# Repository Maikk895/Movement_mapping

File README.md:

Schemat projektu:

Layout płytki:

Wizualizacja:

Gotowy projekt:

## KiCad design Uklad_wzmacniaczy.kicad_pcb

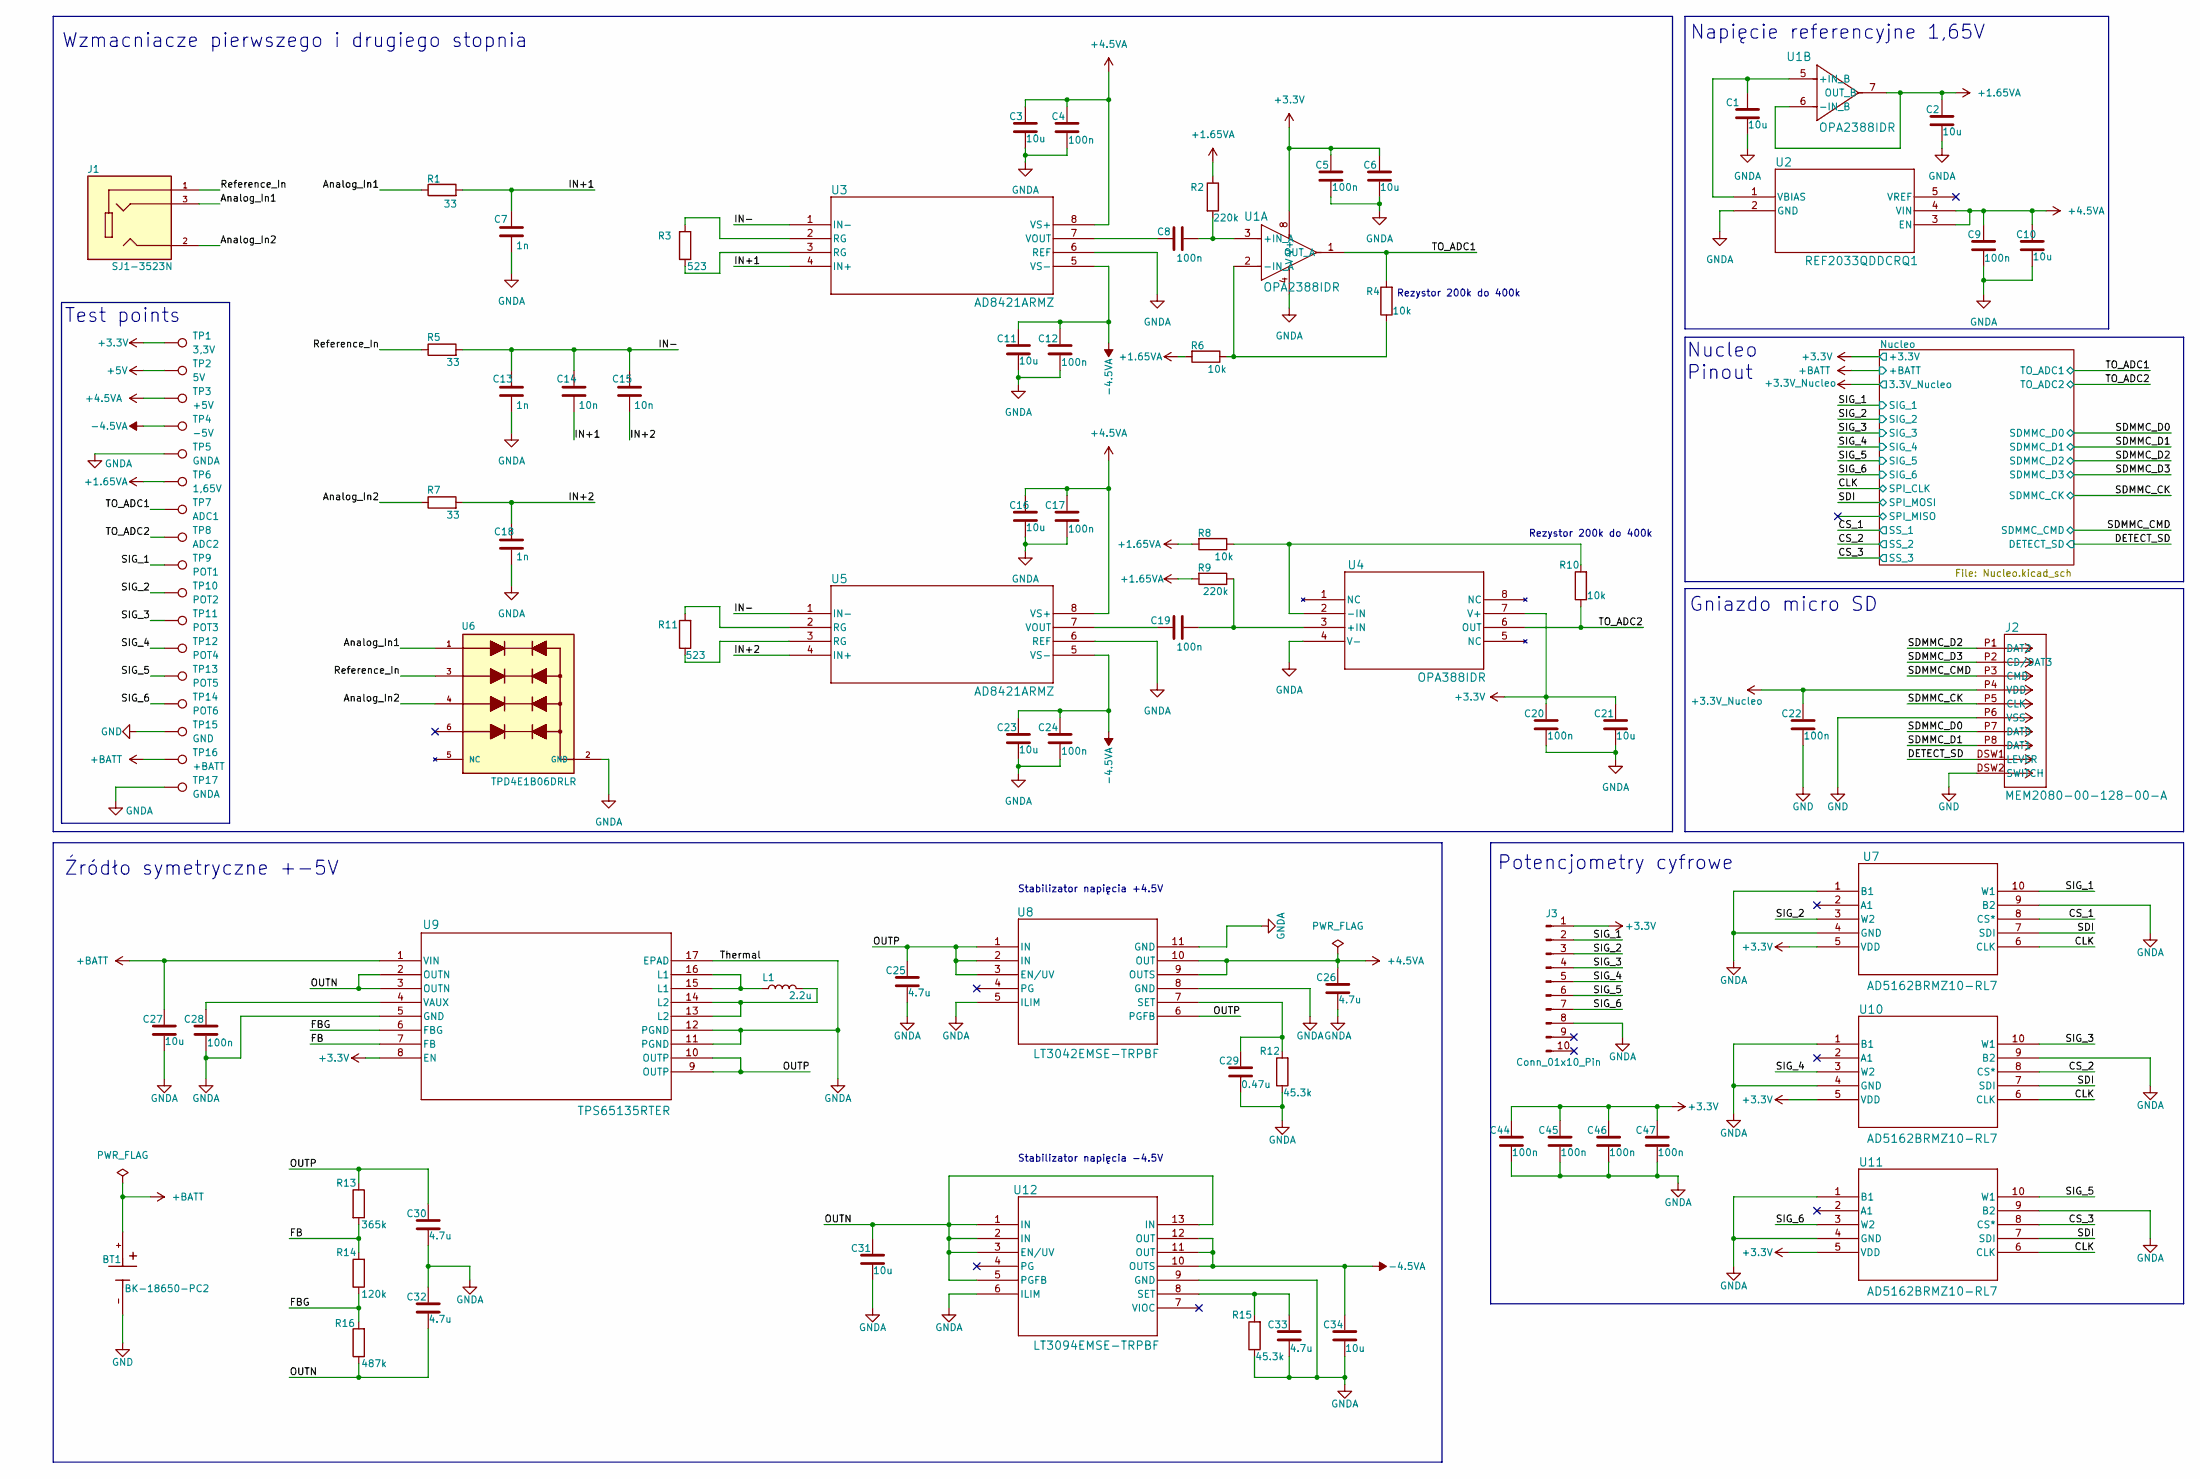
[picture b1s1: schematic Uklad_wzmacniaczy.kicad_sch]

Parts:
BT1: BK-18650-PC2; BAT_BK-18650-PC2; PARTREV F
C1, C2, C3, C6, C10, C11, C16, C21, C23, C27, C31, C34: 10u; C_0603_1608Metric_Pad1.08x0.95mm_HandSolder
C4, C5, C8, C9, C12, C17, C19, C20, C22, C24, C28, C44, C45, C46, C47: 100n; C_0603_1608Metric_Pad1.08x0.95mm_HandSolder
C7, C13, C18: 1n; C_0603_1608Metric_Pad1.08x0.95mm_HandSolder
C14, C15: 10n; C_0603_1608Metric_Pad1.08x0.95mm_HandSolder
C25, C26, C30, C32, C33: 4.7u; C_0603_1608Metric_Pad1.08x0.95mm_HandSolder
C29: 0.47u; C_0603_1608Metric_Pad1.08x0.95mm_HandSolder
J1: SJ1-3523N; CUI_SJ1-3523N; PARTREV 1.05
J2: MEM2080-00-128-00-A; CONN_MEM2080-00-128-00-A_GCT
J3: Conn_01x10_Pin; PinHeader_2x05_P2.54mm_Horizontal
L1: 2.2u; INDC2520X120N
R1, R5, R7: 33; R_0603_1608Metric_Pad0.98x0.95mm_HandSolder
R2, R9: 220k; R_0603_1608Metric_Pad0.98x0.95mm_HandSolder
R3, R11: 523; R_0603_1608Metric_Pad0.98x0.95mm_HandSolder
R4, R6, R8, R10: 10k; R_0603_1608Metric_Pad0.98x0.95mm_HandSolder
R12, R15: 45.3k; R_0603_1608Metric_Pad0.98x0.95mm_HandSolder
R13: 365k; R_0603_1608Metric_Pad0.98x0.95mm_HandSolder
R14: 120k; R_0603_1608Metric_Pad0.98x0.95mm_HandSolder
R16: 487k; R_0603_1608Metric_Pad0.98x0.95mm_HandSolder
TP1: 3,3V; TestPoint_Pad_D1.5mm
TP2: 5V; TestPoint_Pad_D1.5mm
TP3: +5V; TestPoint_Pad_D1.5mm
TP4: -5V; TestPoint_Pad_D1.5mm
TP5, TP17: GNDA; TestPoint_Pad_2.0x2.0mm
TP6: 1,65V; TestPoint_Pad_D1.5mm
TP7: ADC1; TestPoint_Pad_D1.5mm
TP8: ADC2; TestPoint_Pad_D1.5mm
TP9: POT1; TestPoint_Pad_D1.5mm
TP10: POT2; TestPoint_Pad_D1.5mm
TP11: POT3; TestPoint_Pad_D1.5mm
TP12: POT4; TestPoint_Pad_D1.5mm
TP13: POT5; TestPoint_Pad_D1.5mm
TP14: POT6; TestPoint_Pad_D1.5mm
TP15: GND; TestPoint_Pad_2.0x2.0mm
TP16: +BATT; TestPoint_Pad_D1.5mm
U1: OPA2388IDR; D0008A-IPC_A
U2: REF2033QDDCRQ1; SOT-23-THIN-5_DDC_TEX
U3, U5: AD8421ARMZ; RM_8_ADI
U4: OPA388IDR; D8_TEX
U6: TPD4E1B06DRLR; SOT50P160X60-6N; PARTREV E
U7, U10, U11: AD5162BRMZ10-RL7; RM_10_ADI
U8: LT3042EMSE-TRPBF; 05-08-1664_ADI
U9: TPS65135RTER; RTE16_1P7X1P7
U12: LT3094EMSE-TRPBF; MSE_05-08-1666_ADI

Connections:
+1.65VA: C2.1, R2.1, R6.2, R8.2, R9.2, TP6.1 (1_1), U1.6 (-IN_B), U1.7 (OUT_B)
+3.3V: C5.2, C6.1, C20.2, C21.1, C44.1, C45.1, C46.1, C47.1, J3.1, TP1.1 (1_1), U1.8 (V+), U4.7 (V+), U7.5 (VDD), U9.8 (EN), U10.5 (VDD), U11.5 (VDD); also elsewhere on the board
+3.3V_Nucleo: C22.1, J2.P4 (VDD); also elsewhere on the board
+5V: TP2.1 (1_1); also elsewhere on the board
+5VA: C3.1, C4.2, C9.1, C10.1, C16.1, C17.2, C26.1, TP3.1 (1_1), U2.3 (EN), U2.4 (VIN), U3.8 (VS+), U5.8 (VS+), U8.9 (OUTS), U8.10 (OUT)
+BATT: BT1.+, C27.1, TP16.1 (1_1), U9.1 (VIN); also elsewhere on the board
-5VA: C11.1, C12.2, C23.1, C24.2, C34.1, TP4.1 (1_1), U3.5 (VS-), U5.5 (VS-), U12.10 (OUTS), U12.11 (OUT), U12.12 (OUT)
/Analog_In1: J1.3, R1.1, U6.1
/Analog_In2: J1.2, R7.1, U6.4
/CLK: U7.6 (CLK), U10.6 (CLK), U11.6 (CLK); also elsewhere on the board
/CS_1: U7.8 (CS*); also elsewhere on the board
/CS_2: U10.8 (CS*); also elsewhere on the board
/CS_3: U11.8 (CS*); also elsewhere on the board
/DETECT_SD: J2.DSW1 (LEVER); also elsewhere on the board
/FB: R13.2, R14.2, U9.7 (FB)
/FBG: R14.1, R16.2, U9.6 (FBG)
/IN+1: C7.1, C14.2, R1.2, U3.4 (IN+)
/IN+2: C15.2, C18.1, R7.2, U5.4 (IN+)
/IN-: C13.1, C14.1, C15.1, R5.2, U3.1 (IN-), U5.1 (IN-)
/OUTN: C31.1, C32.2, R16.1, U9.2 (OUTN), U9.3 (OUTN), U12.1 (IN), U12.2 (IN), U12.3 (EN/UV), U12.5 (PGFB), U12.13 (IN)
/OUTP: C25.1, C30.1, R13.1, U8.1 (IN), U8.2 (IN), U8.3 (EN/UV), U8.6 (PGFB), U9.9 (OUTP), U9.10 (OUTP)
/Reference_In: J1.1, R5.1, U6.3
/SDI: U7.7 (SDI), U10.7 (SDI), U11.7 (SDI); also elsewhere on the board
/SDMMC_CK: J2.P5 (CLK); also elsewhere on the board
/SDMMC_CMD: J2.P3 (CMD); also elsewhere on the board
/SDMMC_D0: J2.P7 (DAT0); also elsewhere on the board
/SDMMC_D1: J2.P8 (DAT1); also elsewhere on the board
/SDMMC_D2: J2.P1 (DAT2); also elsewhere on the board
/SDMMC_D3: J2.P2 (CD/DAT3); also elsewhere on the board
/SIG_1: J3.2, TP9.1 (1_1), U7.10 (W1); also elsewhere on the board
/SIG_2: J3.3, TP10.1 (1_1), U7.3 (W2); also elsewhere on the board
/SIG_3: J3.4, TP11.1 (1_1), U10.10 (W1); also elsewhere on the board
/SIG_4: J3.5, TP12.1 (1_1), U10.3 (W2); also elsewhere on the board
/SIG_5: J3.6, TP13.1 (1_1), U11.10 (W1); also elsewhere on the board
/SIG_6: J3.7, TP14.1 (1_1), U11.3 (W2); also elsewhere on the board
/TO_ADC1: R4.2, TP7.1 (1_1), U1.1 (OUT_A); also elsewhere on the board
/TO_ADC2: R10.1, TP8.1 (1_1), U4.6 (OUT); also elsewhere on the board
GND: BT1.-, C22.2, J2.DSW2 (SWITCH), J2.P6 (VSS), TP15.1 (1_1); also elsewhere on the board
GNDA: C1.2, C2.2, C3.2, C4.1, C5.1, C6.2, C7.2, C9.2, C10.2, C11.2, C12.1, C13.2, C16.2, C17.1, C18.2, C20.1, C21.2, C23.2, C24.1, C25.2, C26.2, C27.2, C28.1, C29.2, C30.2, C31.2, C32.1, C33.2, C34.2, C44.2, C45.2, C46.2, C47.2, J3.8, R12.1, R15.1, TP5.1 (1_1), TP17.1 (1_1), U1.4 (V-), U2.2 (GND), U3.6 (REF), U4.4 (V-), U5.6 (REF), U6.2 (GND_2), U7.1 (B1), U7.4 (GND), U7.9 (B2), U8.5 (ILIM), U8.8 (GND), U8.11 (GND), U9.5 (GND), U9.11 (PGND), U9.12 (PGND), U9.17 (EPAD), U9.EPAD, U10.1 (B1), U10.4 (GND), U10.9 (B2), U11.1 (B1), U11.4 (GND), U11.9 (B2), U12.6 (ILIM), U12.9 (GND); also elsewhere on the board
unnamed: L1.1, U9.15 (L1), U9.16 (L1)
unnamed: L1.2, U9.13 (L2), U9.14 (L2)
unnamed: R3.1, U3.3 (RG)
unnamed: R3.2, U3.2 (RG)
unnamed: R11.1, U5.3 (RG)
unnamed: R11.2, U5.2 (RG)
unnamed: C8.2, R2.2, U1.3 (+IN_A)
unnamed: R4.1, R6.1, U1.2 (-IN_A)
unnamed: C1.1, U1.5 (+IN_B), U2.1 (VBIAS)
unnamed: C8.1, U3.7 (VOUT)
unnamed: C19.2, R9.1, U4.3 (+IN)
unnamed: R8.1, R10.2, U4.2 (-IN)
unnamed: C19.1, U5.7 (VOUT)
unnamed: C29.1, R12.2, U8.7 (SET)
unnamed: C28.2, U9.4 (VAUX)
unnamed: C33.1, R15.2, U12.8 (SET)

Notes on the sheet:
Napięcie referencyjne 1,65V
Źródło symetryczne +-5V
Stabilizator napięcia -4.5V
Nucleo Pinout
Potencjometry cyfrowe
Gniazdo micro SD
Wzmacniacze pierwszego i drugiego stopnia
Rezystor 200k do 400k
Test points
Stabilizator napięcia +4.5V

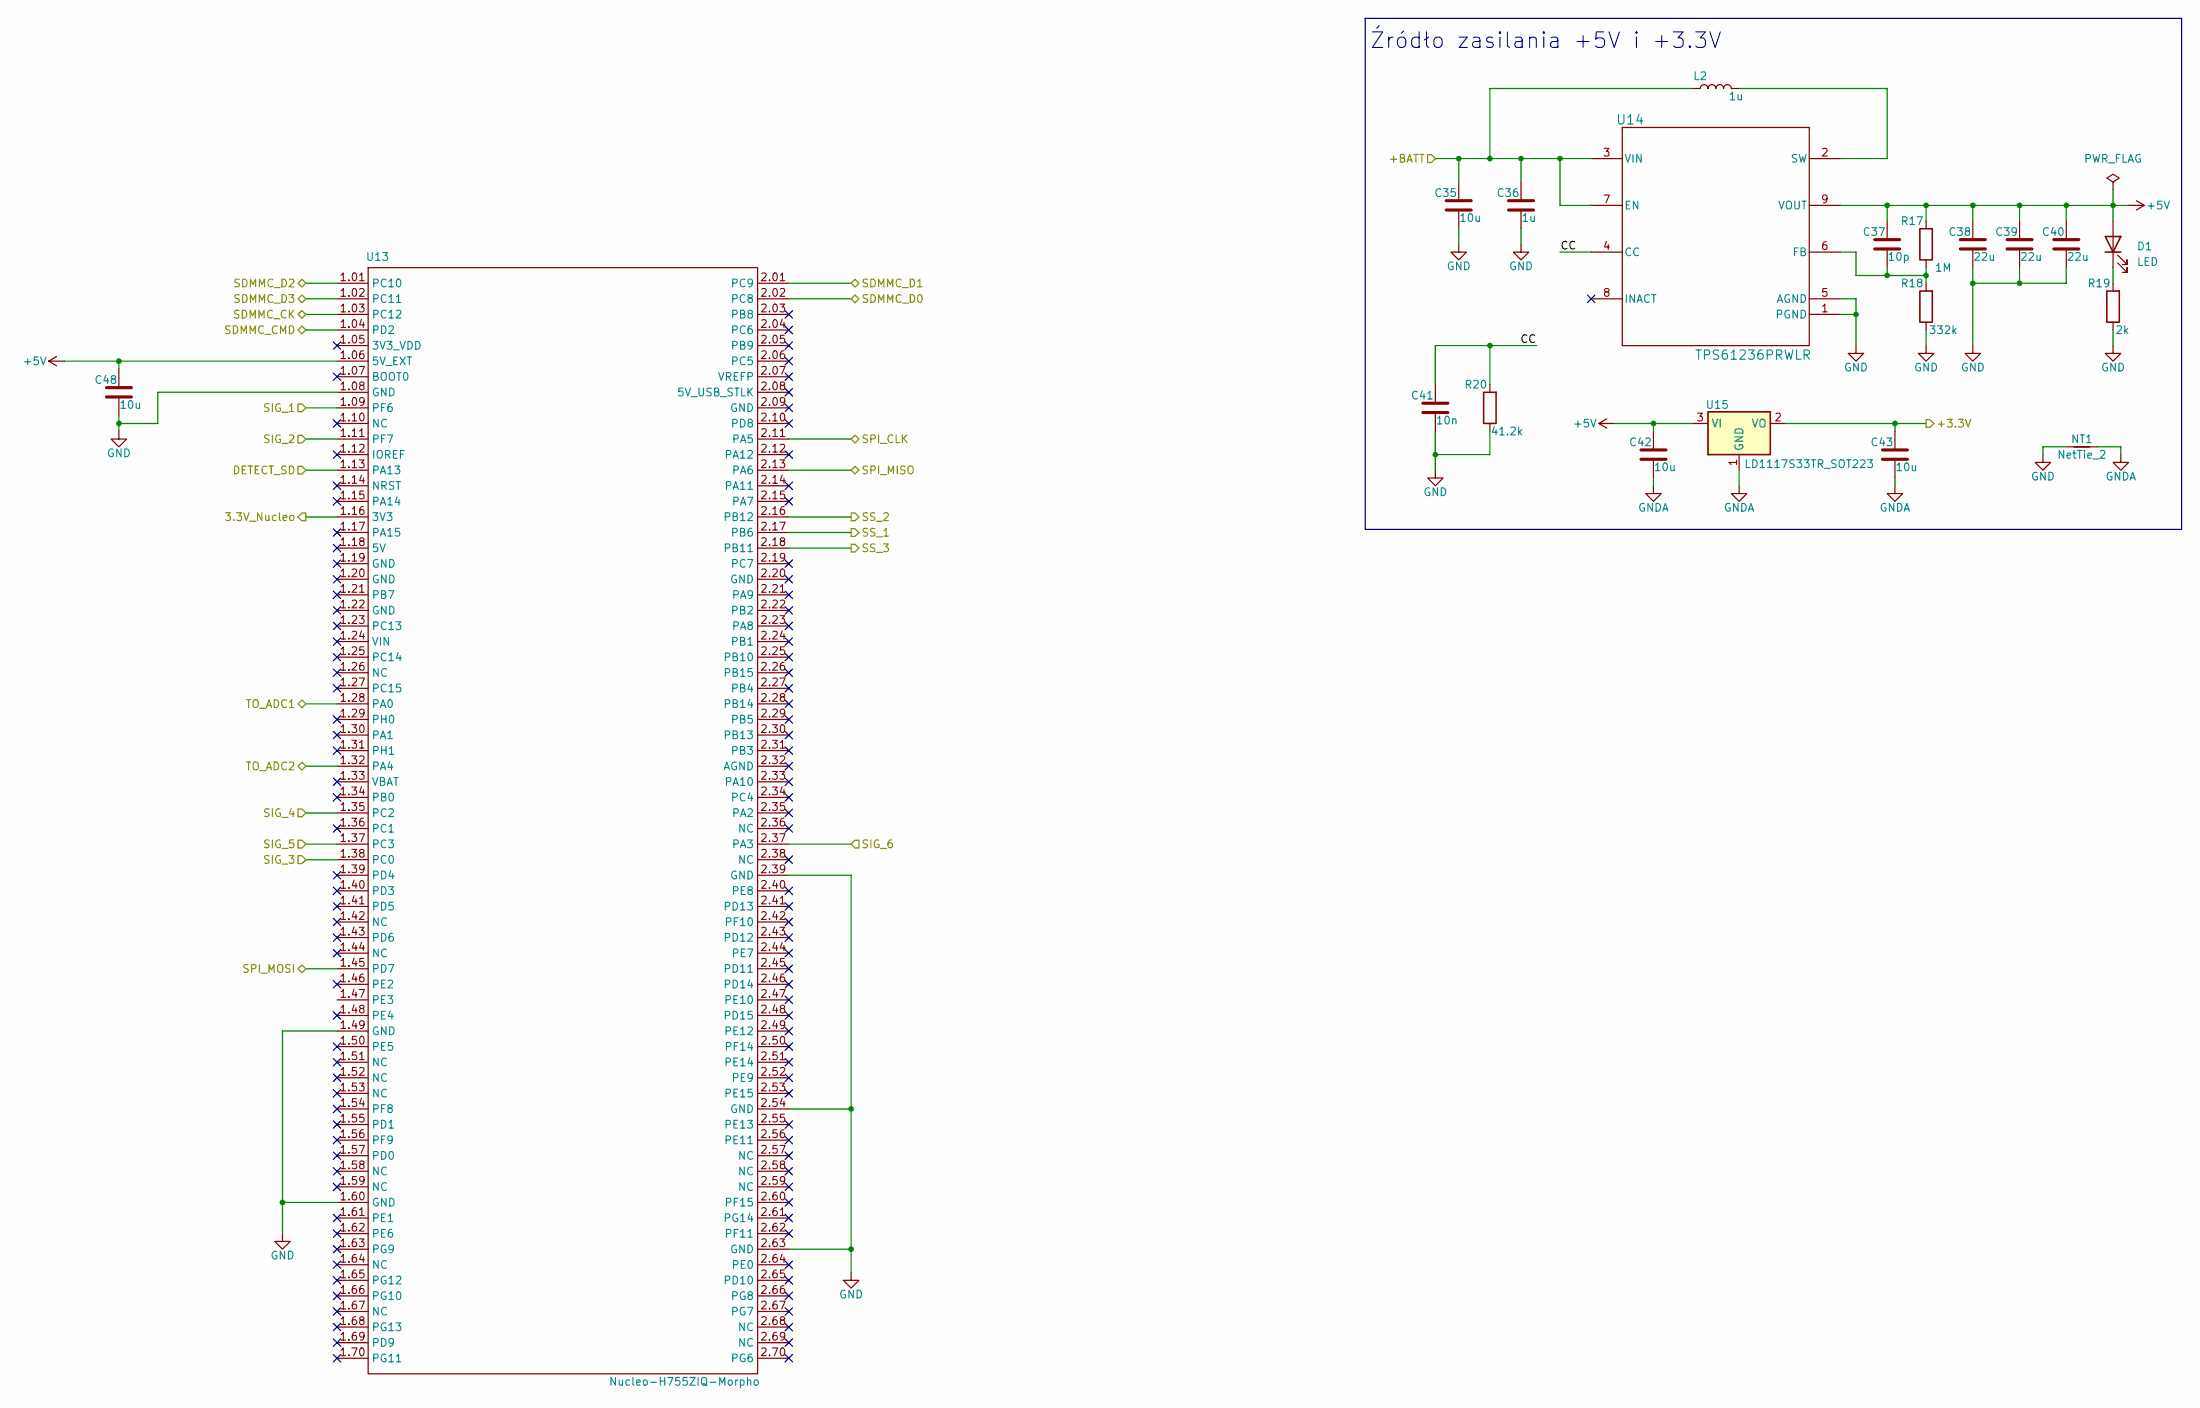
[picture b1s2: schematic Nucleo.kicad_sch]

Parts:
C35, C42, C43, C48: 10u; C_0603_1608Metric_Pad1.08x0.95mm_HandSolder
C36: 1u; C_0603_1608Metric_Pad1.08x0.95mm_HandSolder
C37: 10p; C_0603_1608Metric_Pad1.08x0.95mm_HandSolder
C38, C39, C40: 22u; C_0603_1608Metric_Pad1.08x0.95mm_HandSolder
C41: 10n; C_0603_1608Metric_Pad1.08x0.95mm_HandSolder
D1: LED; LED_0805_2012Metric_Pad1.15x1.40mm_HandSolder
L2: 1u; IND_SPM6530T-1R0M120
NT1: NetTie_2; NetTie-2_SMD_Pad0.5mm
R17: 1M; R_0603_1608Metric_Pad0.98x0.95mm_HandSolder
R18: 332k; R_0603_1608Metric_Pad0.98x0.95mm_HandSolder
R19: 2k; R_0603_1608Metric_Pad0.98x0.95mm_HandSolder
R20: 41.2k; R_0603_1608Metric_Pad0.98x0.95mm_HandSolder
U13: Nucleo-H755ZIQ-Morpho
U14: TPS61236PRWLR; RWL0009A
U15: LD1117S33TR_SOT223; SOT-223-3_TabPin2

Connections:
+3.3V: C43.1, U15.2 (VO); also elsewhere on the board
+3.3V_Nucleo: U13.1.16 (3V3); also elsewhere on the board
+5V: C37.1, C38.1, C39.1, C40.1, C42.1, C48.1, D1.2 (A), R17.2, U13.1.06 (5V_EXT), U14.9 (VOUT), U15.3 (VI); also elsewhere on the board
+BATT: C35.1, C36.1, L2.1, U14.3 (VIN), U14.7 (EN); also elsewhere on the board
/CLK: U13.2.11 (PA5); also elsewhere on the board
/CS_1: U13.2.17 (PB6); also elsewhere on the board
/CS_2: U13.2.16 (PB12); also elsewhere on the board
/CS_3: U13.2.18 (PB11); also elsewhere on the board
/DETECT_SD: U13.1.13 (PA13); also elsewhere on the board
/Nucleo/CC: C41.1, R20.2, U14.4 (CC)
/Nucleo/SPI_MISO: U13.2.13 (PA6)
/SDI: U13.1.45 (PD7); also elsewhere on the board
/SDMMC_CK: U13.1.03 (PC12); also elsewhere on the board
/SDMMC_CMD: U13.1.04 (PD2); also elsewhere on the board
/SDMMC_D0: U13.2.02 (PC8); also elsewhere on the board
/SDMMC_D1: U13.2.01 (PC9); also elsewhere on the board
/SDMMC_D2: U13.1.01 (PC10); also elsewhere on the board
/SDMMC_D3: U13.1.02 (PC11); also elsewhere on the board
/SIG_1: U13.1.09 (PF6); also elsewhere on the board
/SIG_2: U13.1.11 (PF7); also elsewhere on the board
/SIG_3: U13.1.38 (PC0); also elsewhere on the board
/SIG_4: U13.1.35 (PC2); also elsewhere on the board
/SIG_5: U13.1.37 (PC3); also elsewhere on the board
/SIG_6: U13.2.37 (PA3); also elsewhere on the board
/TO_ADC1: U13.1.28 (PA0); also elsewhere on the board
/TO_ADC2: U13.1.32 (PA4); also elsewhere on the board
GND: C35.2, C36.2, C38.2, C39.2, C40.2, C41.2, C48.2, NT1.1, R18.1, R19.1, R20.1, U13.1.08 (GND), U13.1.49 (GND), U13.1.60 (GND), U13.2.39 (GND), U13.2.54 (GND), U13.2.63 (GND), U14.1 (PGND), U14.5 (AGND); also elsewhere on the board
GNDA: C42.2, C43.2, NT1.2, U15.1 (GND); also elsewhere on the board
unnamed: D1.1 (K), R19.2
unnamed: C37.2, R17.1, R18.2, U14.6 (FB)
unnamed: L2.2, U14.2 (SW)

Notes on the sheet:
Źródło zasilania +5V i +3.3V

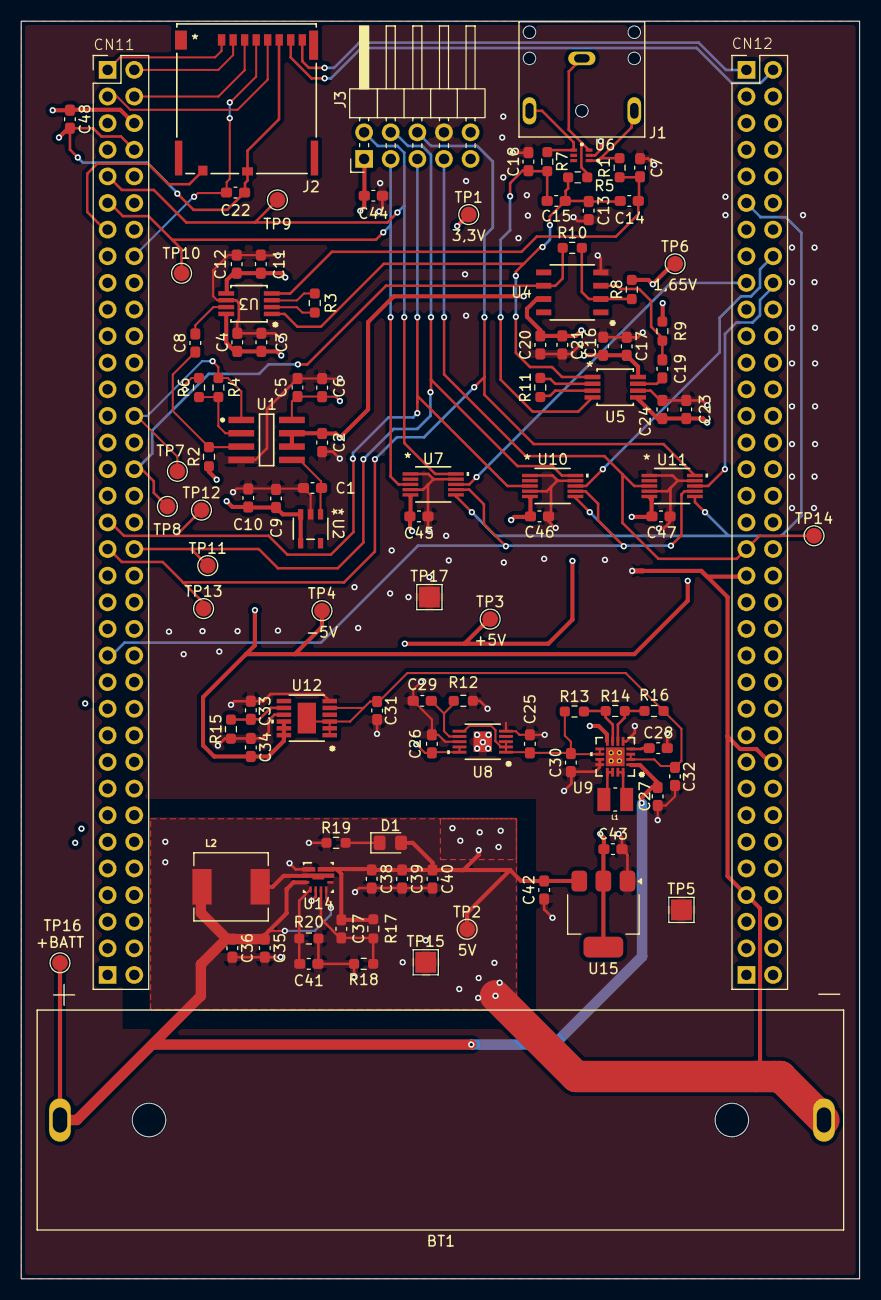
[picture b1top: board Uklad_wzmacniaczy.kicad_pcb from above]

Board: 4 copper layers, 80.0 x 120.0 mm, 108 parts (0 on the bottom side), 59 nets.

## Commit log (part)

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2026-04-08 Footprint and symbol for Nucleo-h755ZIQ added
2026-04-14 PCB layout first commit, minor fix in schematic
2026-04-15 Schematic minor change Vbat -> 3.3V, PCB layout: +5V, -5V
2026-05-25 New STM footprint, changed PCB layout, added pin connector
2026-05-27 Nucleo-shield pins change
2026-06-24 Layout major change, .gitignore added
2026-06-29 Layout and schematic minor changes
